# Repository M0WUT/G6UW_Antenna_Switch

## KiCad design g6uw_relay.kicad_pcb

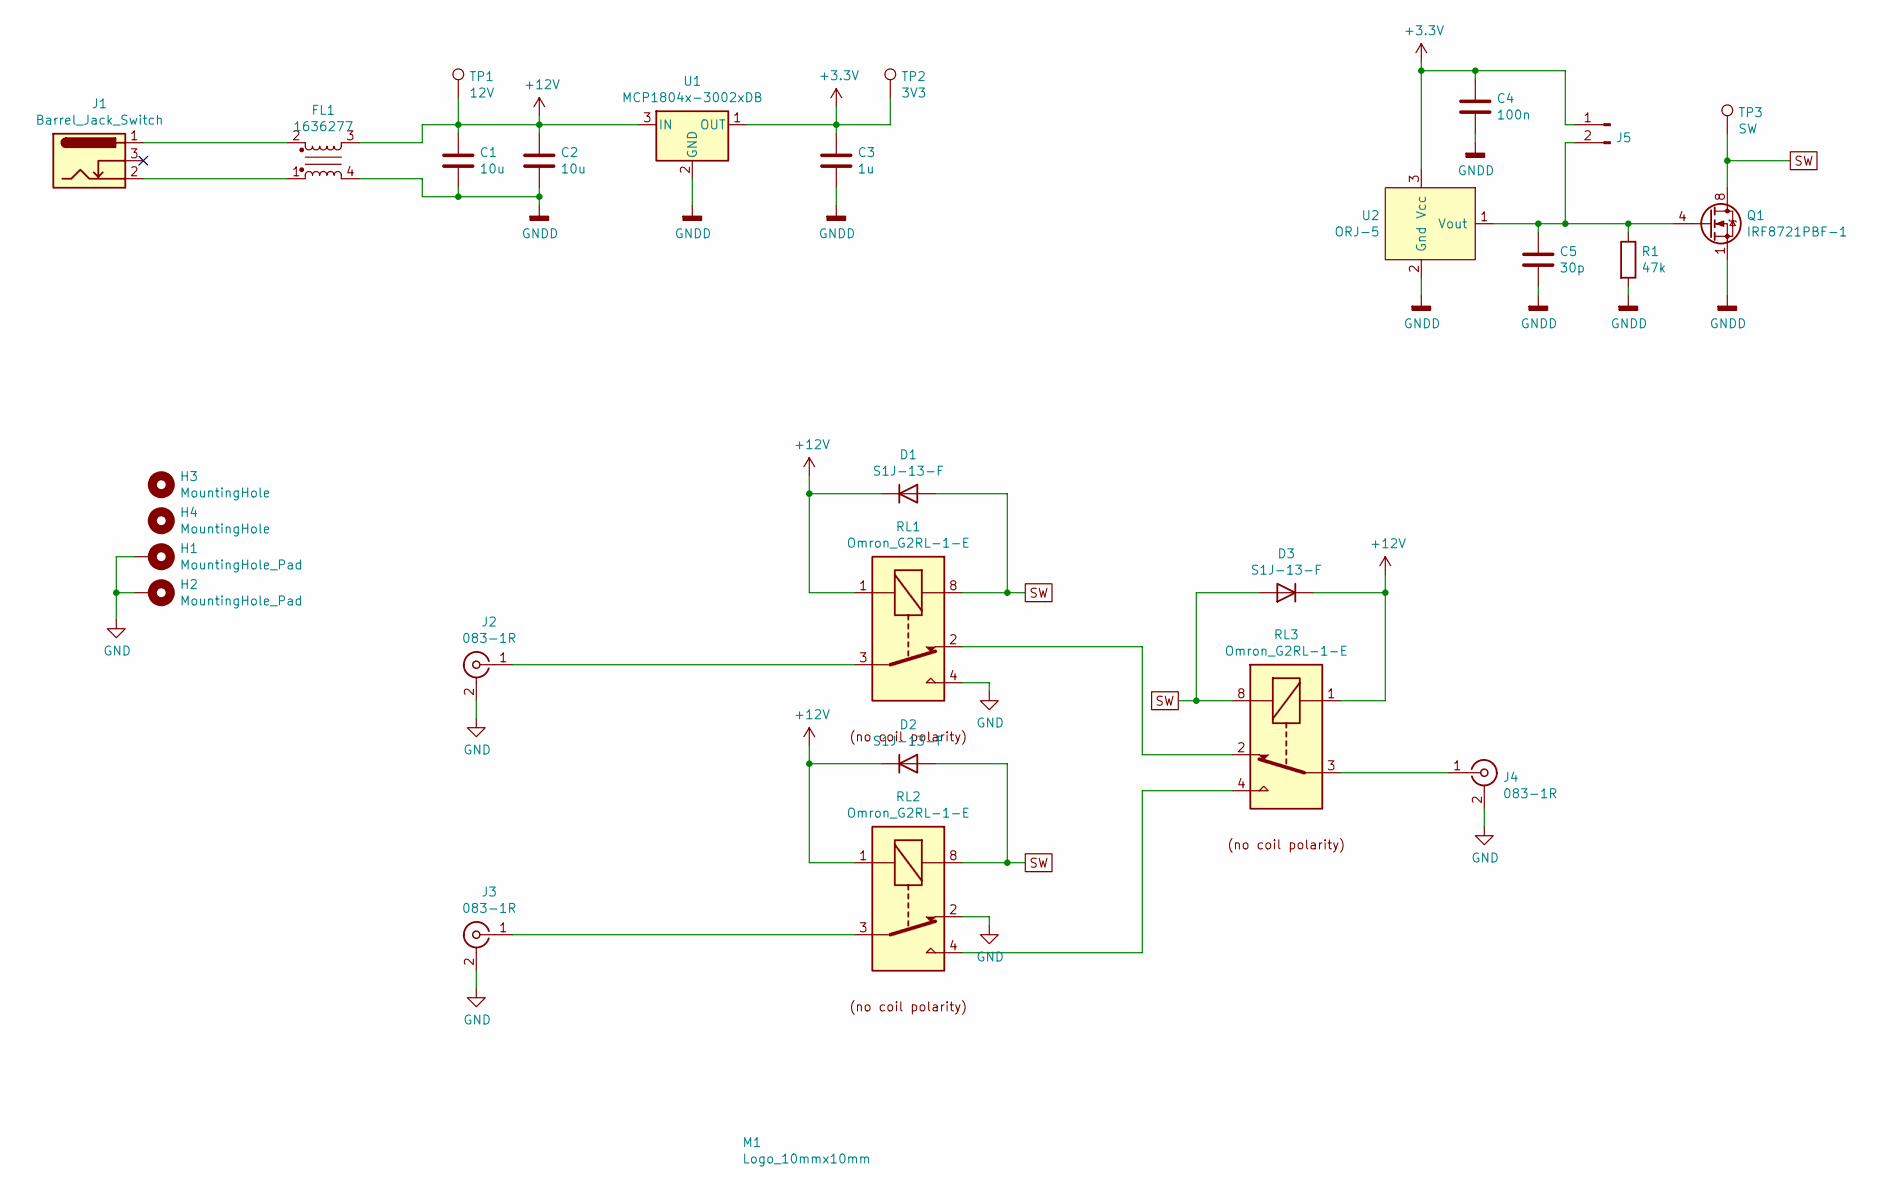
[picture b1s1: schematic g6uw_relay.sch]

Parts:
C1, C2: 10u; C_1206_3216Metric
C3: 1u; C_0805_2012Metric
C4: 100n; C_0805_2012Metric
C5: 30p; C_0805_2012Metric
D1, D2, D3: S1J-13-F; D_SMA
FL1: 1636277; L_CommonMode_Wuerth_WE-SL2
H1, H2: MountingHole_Pad; MountingHole_3.2mm_M3_Pad_Via
H3, H4: MountingHole; MountingHole_3.2mm_M3_ISO14580
J1: Barrel_Jack_Switch; Barrel-Jack_Cliff_FC681478_TH
J2, J3, J4: 083-1R; SO239_Amphenol_083-1R
J5: Conn_01x02_Male; PinHeader_1x02_P2.54mm_Vertical
M1: Logo_10mmx10mm; Logo_10mmx10mm_Monocle
Q1: IRF8721PBF-1; SOIC-8_3.9x4.9mm_P1.27mm
R1: 47k; R_0805_2012Metric
RL1, RL2, RL3: Omron_G2RL-1-E
TP1: 12V; TestPoint_Pad_D2.0mm
TP2: 3V3; TestPoint_Pad_D2.0mm
TP3: SW; TestPoint_Pad_D2.0mm
U1: MCP1804x-3002xDB; SOT-223-3_TabPin2
U2: ORJ-5; TOSLINK_Cliff_ORJ-5

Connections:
+3V3: C3.1, C4.1, J5.1, TP2.1, U1.1 (OUT), U2.3 (Vcc)
+12V: C1.1, C2.1, D1.1 (K), D2.1 (K), D3.1 (K), FL1.3, RL1.1, RL2.1, RL3.1, TP1.1, U1.3 (IN)
GND: H1.1, H2.1, J2.2 (Ext), J3.2 (Ext), J4.2 (Ext), RL1.4, RL1.5, RL2.2, RL2.7
GNDD: C1.2, C2.2, C3.2, C4.2, C5.2, FL1.4, Q1.1 (S), Q1.2 (S), Q1.3 (S), R1.2, U1.2 (GND), U2.2 (Gnd)
unnamed: C5.1, J5.2, Q1.4 (G), R1.1, U2.1 (Vout)
unnamed: FL1.1, J1.2
unnamed: FL1.2, J1.1
unnamed: J2.1 (In), RL1.3, RL1.6
unnamed: J3.1 (In), RL2.3, RL2.6
unnamed: J4.1 (In), RL3.3, RL3.6
unnamed: RL1.2, RL1.7, RL3.2, RL3.7
unnamed: RL2.4, RL2.5, RL3.4, RL3.5
SW: D1.2 (A), D2.2 (A), D3.2 (A), Q1.5 (D), Q1.6 (D), Q1.7 (D), Q1.8 (D), RL1.8, RL2.8, RL3.8, TP3.1

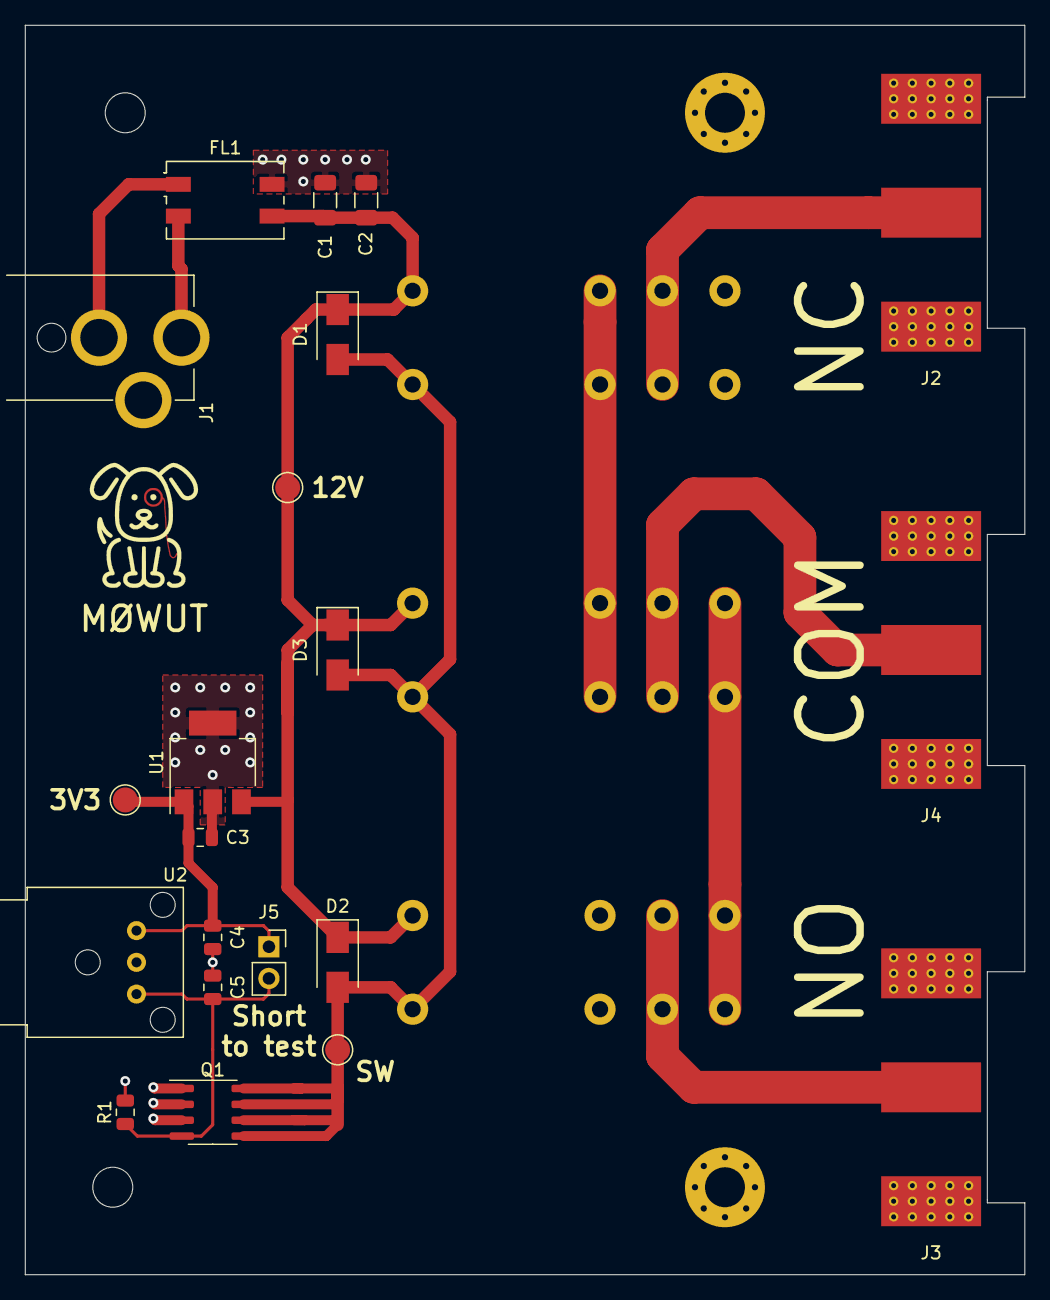
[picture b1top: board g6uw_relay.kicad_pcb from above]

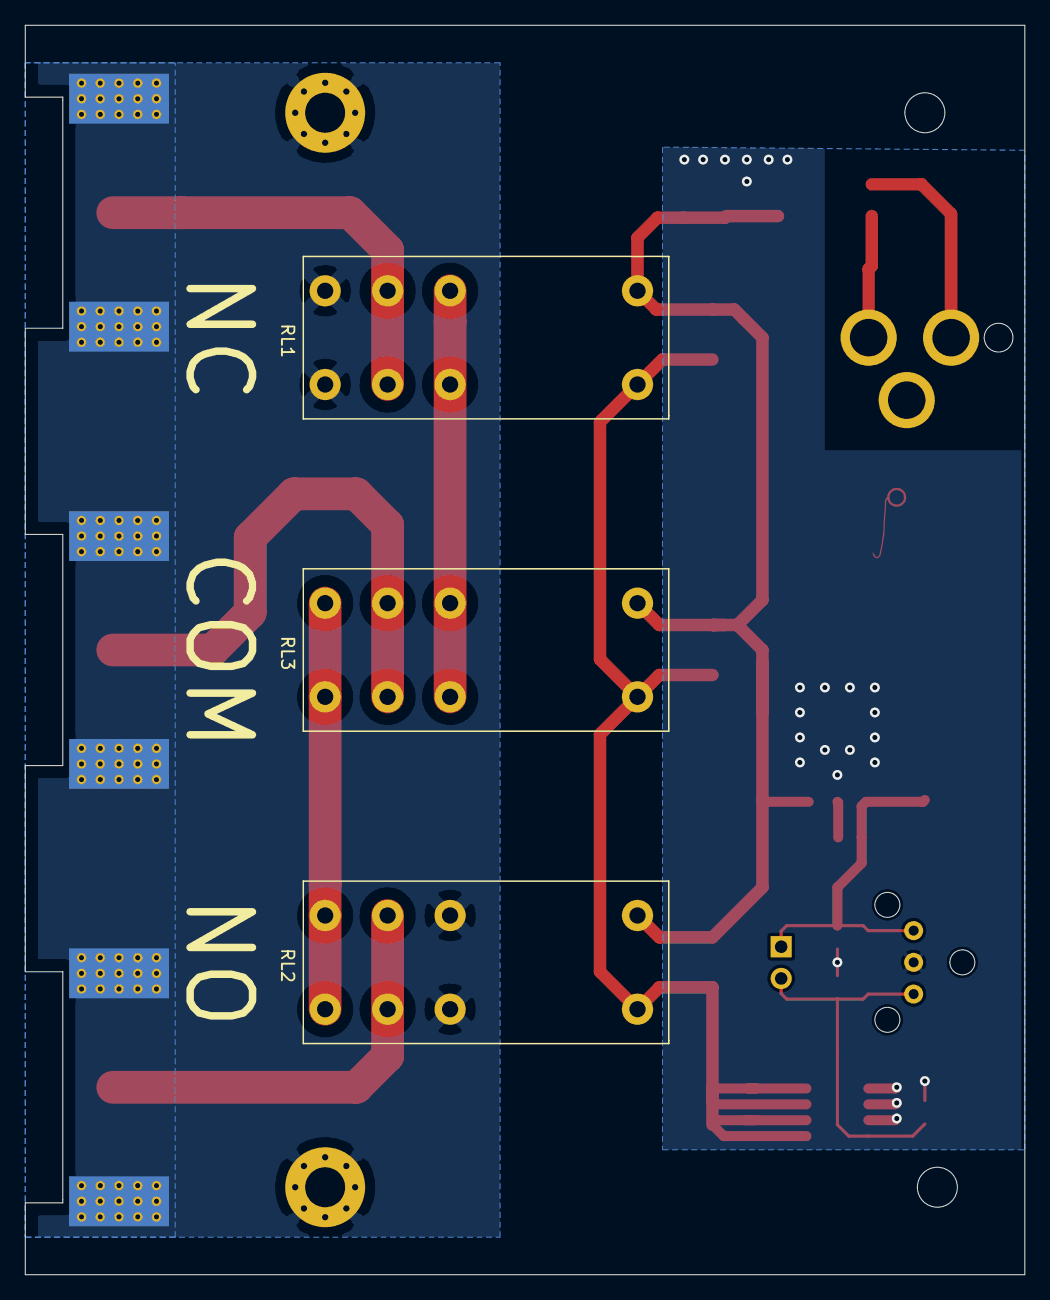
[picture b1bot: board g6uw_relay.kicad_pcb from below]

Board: 2 copper layers, 80.0 x 100.0 mm, 29 parts (3 on the bottom side), 13 nets.

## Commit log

2020-07-04 First pass
2020-07-04 Added 3D models
2020-07-05 Added front and back panels
2020-07-12 Version sent to JLCPCB
